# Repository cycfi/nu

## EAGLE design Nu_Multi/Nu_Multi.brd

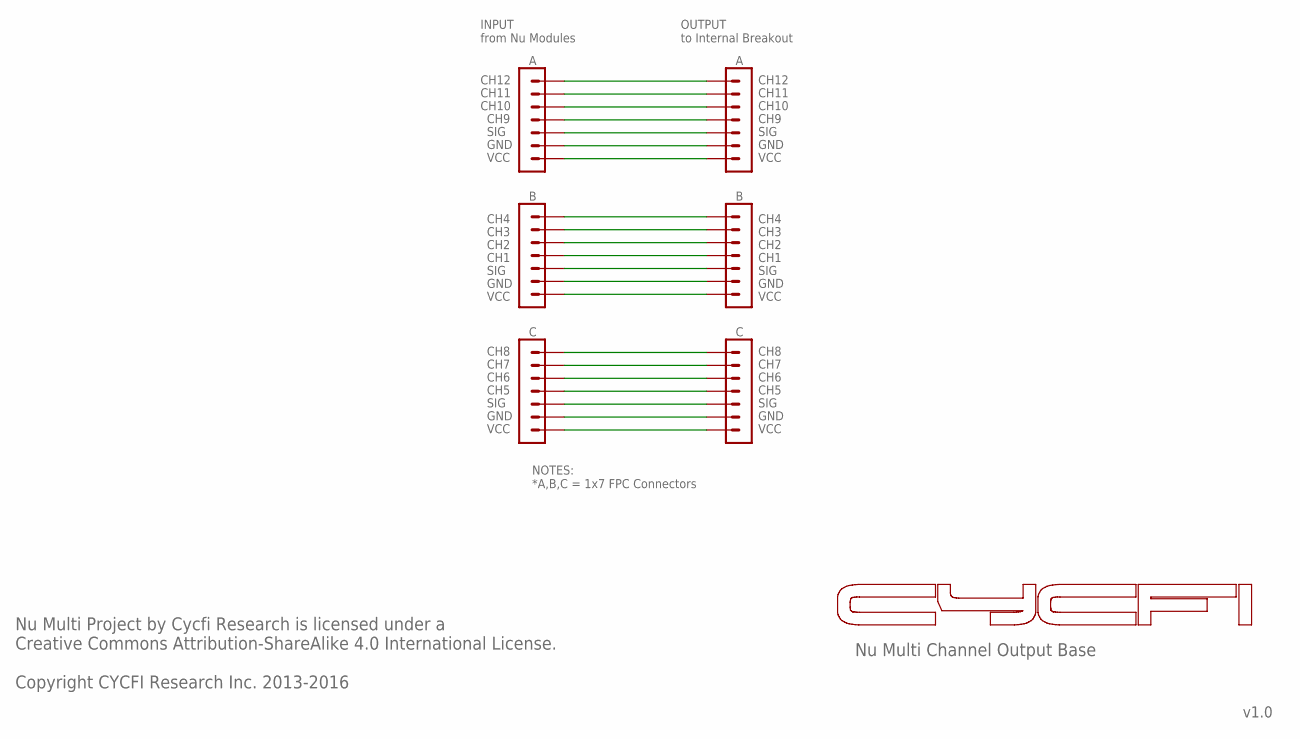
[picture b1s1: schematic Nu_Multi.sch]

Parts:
H1, H2, H3, H4, H5, H6: 7P_ZIF_59453-071110EDHLF

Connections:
GND: H1.P$6 (6), H2.P$6 (6), H3.P$6 (6), H4.P$6 (6), H5.P$6 (6), H6.P$6 (6)
unnamed: H5.P$1 (1), H6.P$1 (1)
unnamed: H5.P$2 (2), H6.P$2 (2)
unnamed: H5.P$3 (3), H6.P$3 (3)
unnamed: H5.P$4 (4), H6.P$4 (4)
unnamed: H5.P$5 (5), H6.P$5 (5)
unnamed: H5.P$7 (7), H6.P$7 (7)
unnamed: H2.P$7 (7), H4.P$7 (7)
unnamed: H2.P$5 (5), H4.P$5 (5)
unnamed: H2.P$4 (4), H4.P$4 (4)
unnamed: H2.P$3 (3), H4.P$3 (3)
unnamed: H2.P$2 (2), H4.P$2 (2)
unnamed: H2.P$1 (1), H4.P$1 (1)
unnamed: H1.P$7 (7), H3.P$7 (7)
unnamed: H1.P$5 (5), H3.P$5 (5)
unnamed: H1.P$4 (4), H3.P$4 (4)
unnamed: H1.P$3 (3), H3.P$3 (3)
unnamed: H1.P$2 (2), H3.P$2 (2)
unnamed: H1.P$1 (1), H3.P$1 (1)

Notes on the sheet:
CH4
CH3
CH2
CH1
SIG
GND
VCC
CH8
CH7
CH6
CH5
CH12
CH11
CH10
CH9
Nu Multi Channel Output Base
v1.0
Nu Multi Project by Cycfi Research is licensed under a Creative Commons Attribution-ShareAlike 4.0 International License. Copyright CYCFI Research Inc. 2013-2016
INPUT from Nu Modules
OUTPUT to Internal Breakout
NOTES: *A,B,C = 1x7 FPC Connectors

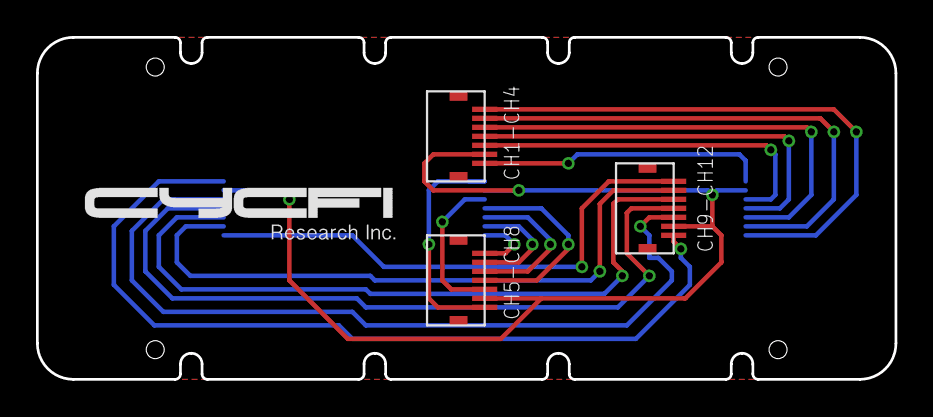
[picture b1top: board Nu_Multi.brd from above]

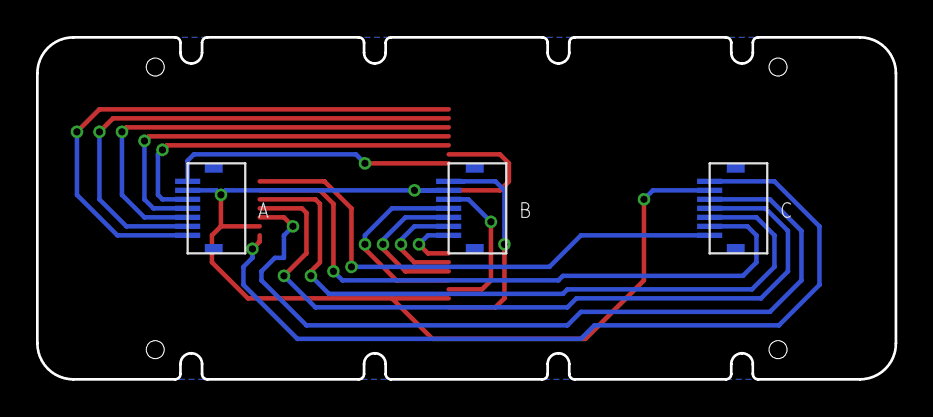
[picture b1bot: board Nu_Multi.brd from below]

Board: 2 copper layers, 47.7 x 19.0 mm, 6 parts (3 on the bottom side), 19 nets.
